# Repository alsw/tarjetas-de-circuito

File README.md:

# tarjetas-de-circuito
Diversas tarjetas de circuito y escudos diseñados por el equipo de ALSW

- Due VGA Shield:
Se trata de un escudo para Arduino Due que agrega un puerto VGA, salida de audio y adaptador de memoria SD. Ideal para demos y proyectos multimedia que requieren audio y video. El escudo no cubre completamente al Due, solo emplea los pines necesarios.

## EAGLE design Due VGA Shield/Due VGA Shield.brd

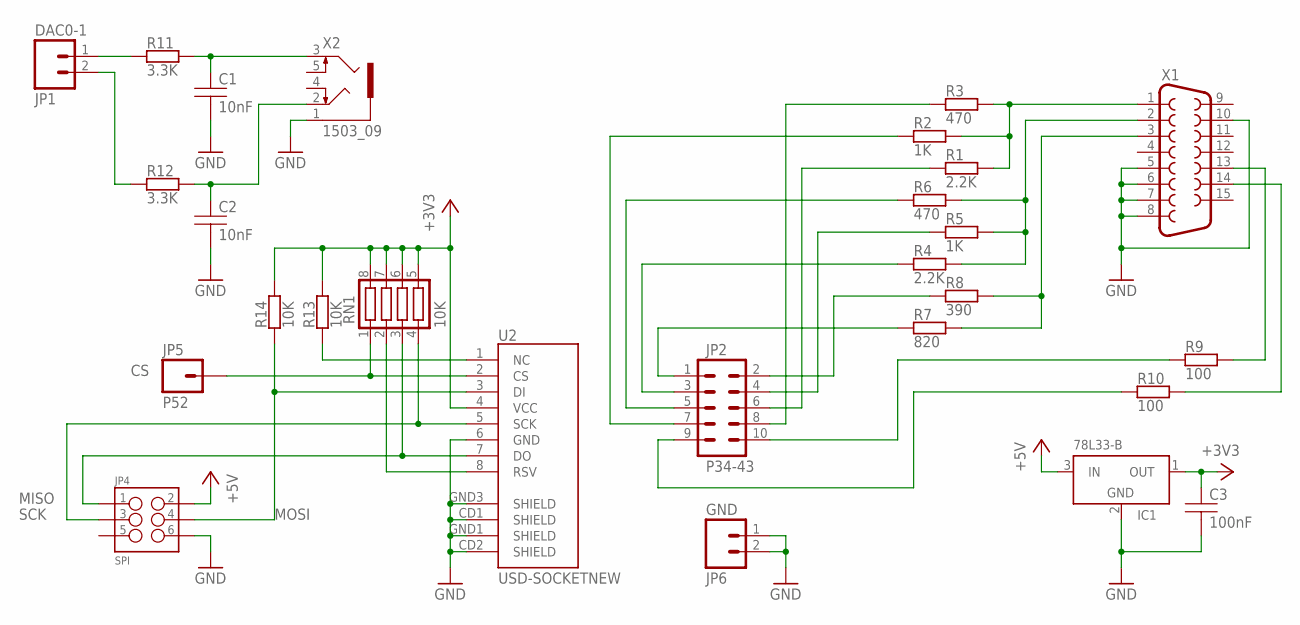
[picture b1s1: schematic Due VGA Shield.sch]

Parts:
C1, C2: 10nF; SMD-2012
C3: 100nF; SMD-2012
IC1: 78L33-B; TO-92/M
JP1: DAC0-1; 1X02
JP2: P34-43; AVR_ICSP
JP4: SPI; 2X3
JP5: P52; 1X01
JP6: GND; 1X02
R1, R4: 2.2K; SMD-2012
R2, R5: 1K; SMD-2012
R3, R6: 470; SMD-2012
R7: 820; SMD-2012
R8: 390; SMD-2012
R9, R10: 100; SMD-2012
R11, R12: 3.3K; SMD-2012
R13, R14: 10K; SMD-2012
RN1: 10K; CTS742C083
U2: USD-SOCKETNEW; MICRO-SD-SOCKET-PP
X1: F15HDH; HDF15H
X2: 1503_09

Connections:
+3V3: C3.P$1 (1), IC1.1 (OUT), R13.P$1, R14.P$1, RN1.5, RN1.6, RN1.7, RN1.8, U2.4 (VCC)
+5V: IC1.3 (IN), JP4.2
CS: JP5.1, RN1.1, U2.2 (CS)
GND: C1.P$2 (2), C2.P$2 (2), C3.P$2 (2), IC1.2 (GND), JP4.6, JP6.1, JP6.2, U2.6 (GND), U2.CD1 (SHIELD), U2.CD2 (SHIELD), U2.GND1 (SHIELD), U2.GND3 (SHIELD), X1.5, X1.6, X1.7, X1.8, X1.10, X2.1
MISO: JP4.1, RN1.3, U2.7 (DO)
MOSI: JP4.4, R14.P$2, U2.3 (DI)
unnamed: R9.P$1, X1.13
unnamed: R10.P$1, X1.14
unnamed: R1.P$1, R2.P$1, R3.P$1, X1.1
unnamed: R4.P$1, R5.P$1, R6.P$1, X1.2
unnamed: R7.P$1, R8.P$1, X1.3
unnamed: C1.P$1 (1), R11.P$1, X2.3
unnamed: C2.P$1 (1), R12.P$1, X2.2
unnamed: JP2.1, R7.P$2
unnamed: JP2.2, R8.P$2
unnamed: JP2.3, R4.P$2
unnamed: JP2.4, R5.P$2
unnamed: JP2.5, R6.P$2
unnamed: JP2.6, R1.P$2
unnamed: JP2.7, R2.P$2
unnamed: JP2.8, R3.P$2
unnamed: JP1.1, R11.P$2
unnamed: JP1.2, R12.P$2
unnamed: JP2.9, R10.P$2
unnamed: JP2.10, R9.P$2
unnamed: RN1.2, U2.8 (RSV)
unnamed: R13.P$2, U2.1 (NC)
SCK: JP4.3, RN1.4, U2.5 (SCK)

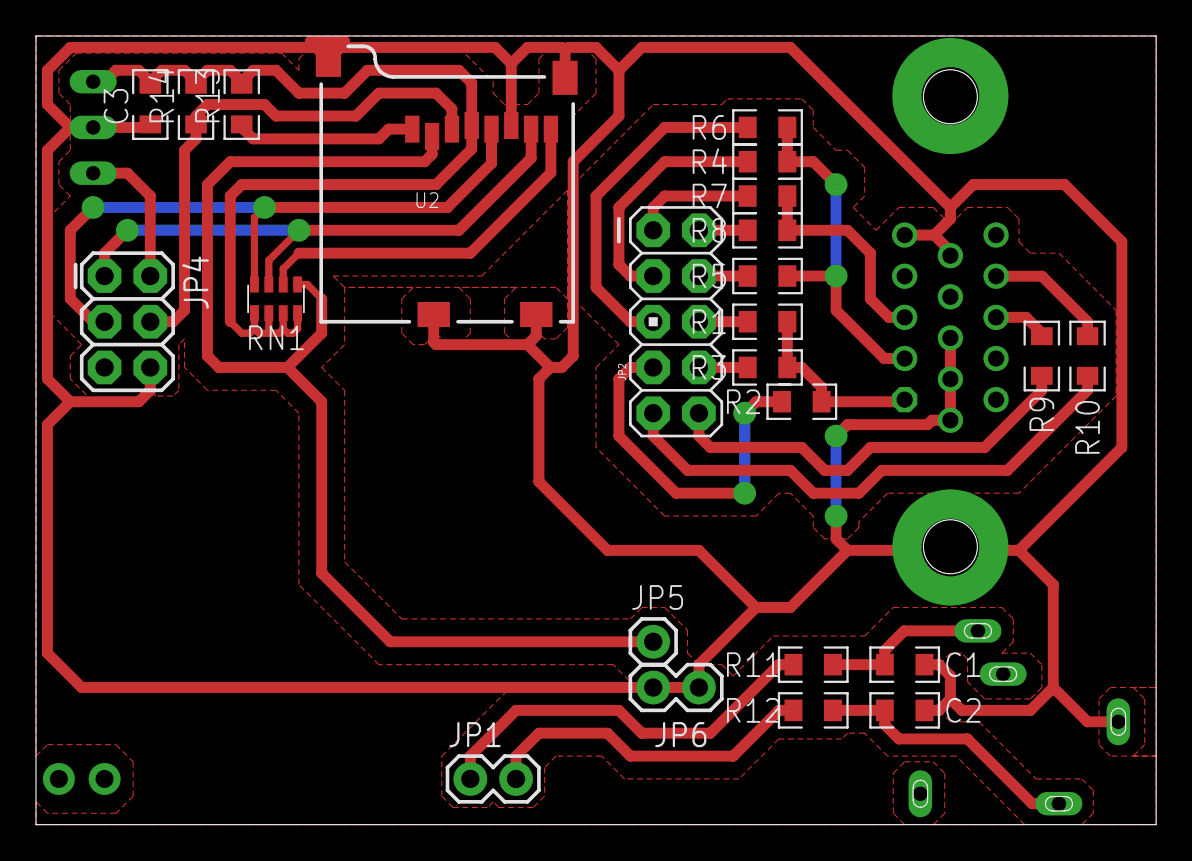
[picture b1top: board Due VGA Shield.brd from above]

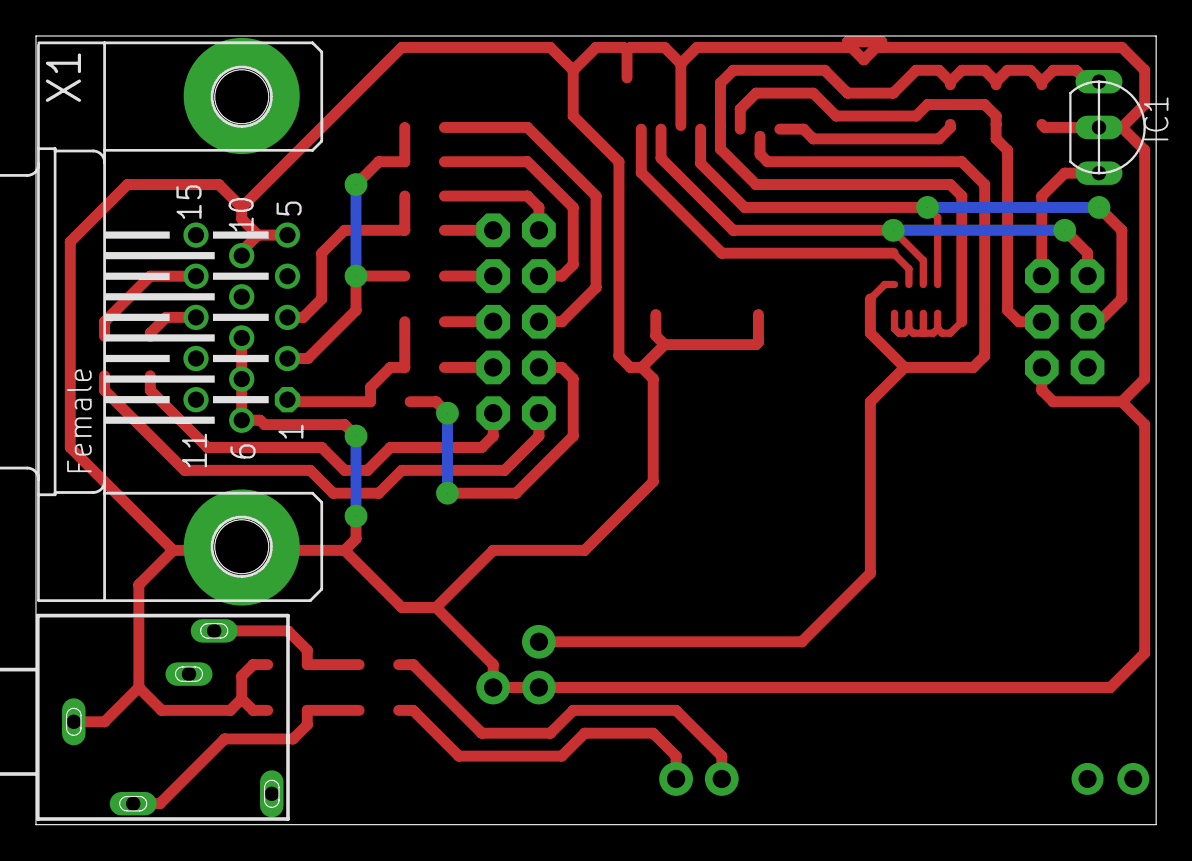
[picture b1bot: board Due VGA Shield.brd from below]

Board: 2 copper layers, 62.2 x 43.8 mm, 27 parts (3 on the bottom side), 28 nets.

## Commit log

2015-04-14 Subidos los archivos del escudo VGA para Due y agregado .gitignore para eagle
2015-04-14 Agregado archivo readme

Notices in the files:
parts and their libraries:
SparkFun-Connectors: Licensing: CC v3.0 Share-Alike You are welcome to use this library for commercial purposes.
